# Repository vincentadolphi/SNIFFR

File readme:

SNIFFR® by Studio IKG

The SNIFFR® is a multifunctional sensorplatform designed to monitor and communicate airquality.
In an effort to increase ventilation window and decrease aerosols.

If there's no vague vase in your life, it's not worth it.
~ Studio IKG

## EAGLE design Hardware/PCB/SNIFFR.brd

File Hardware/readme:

All files have been created with Rhino6.

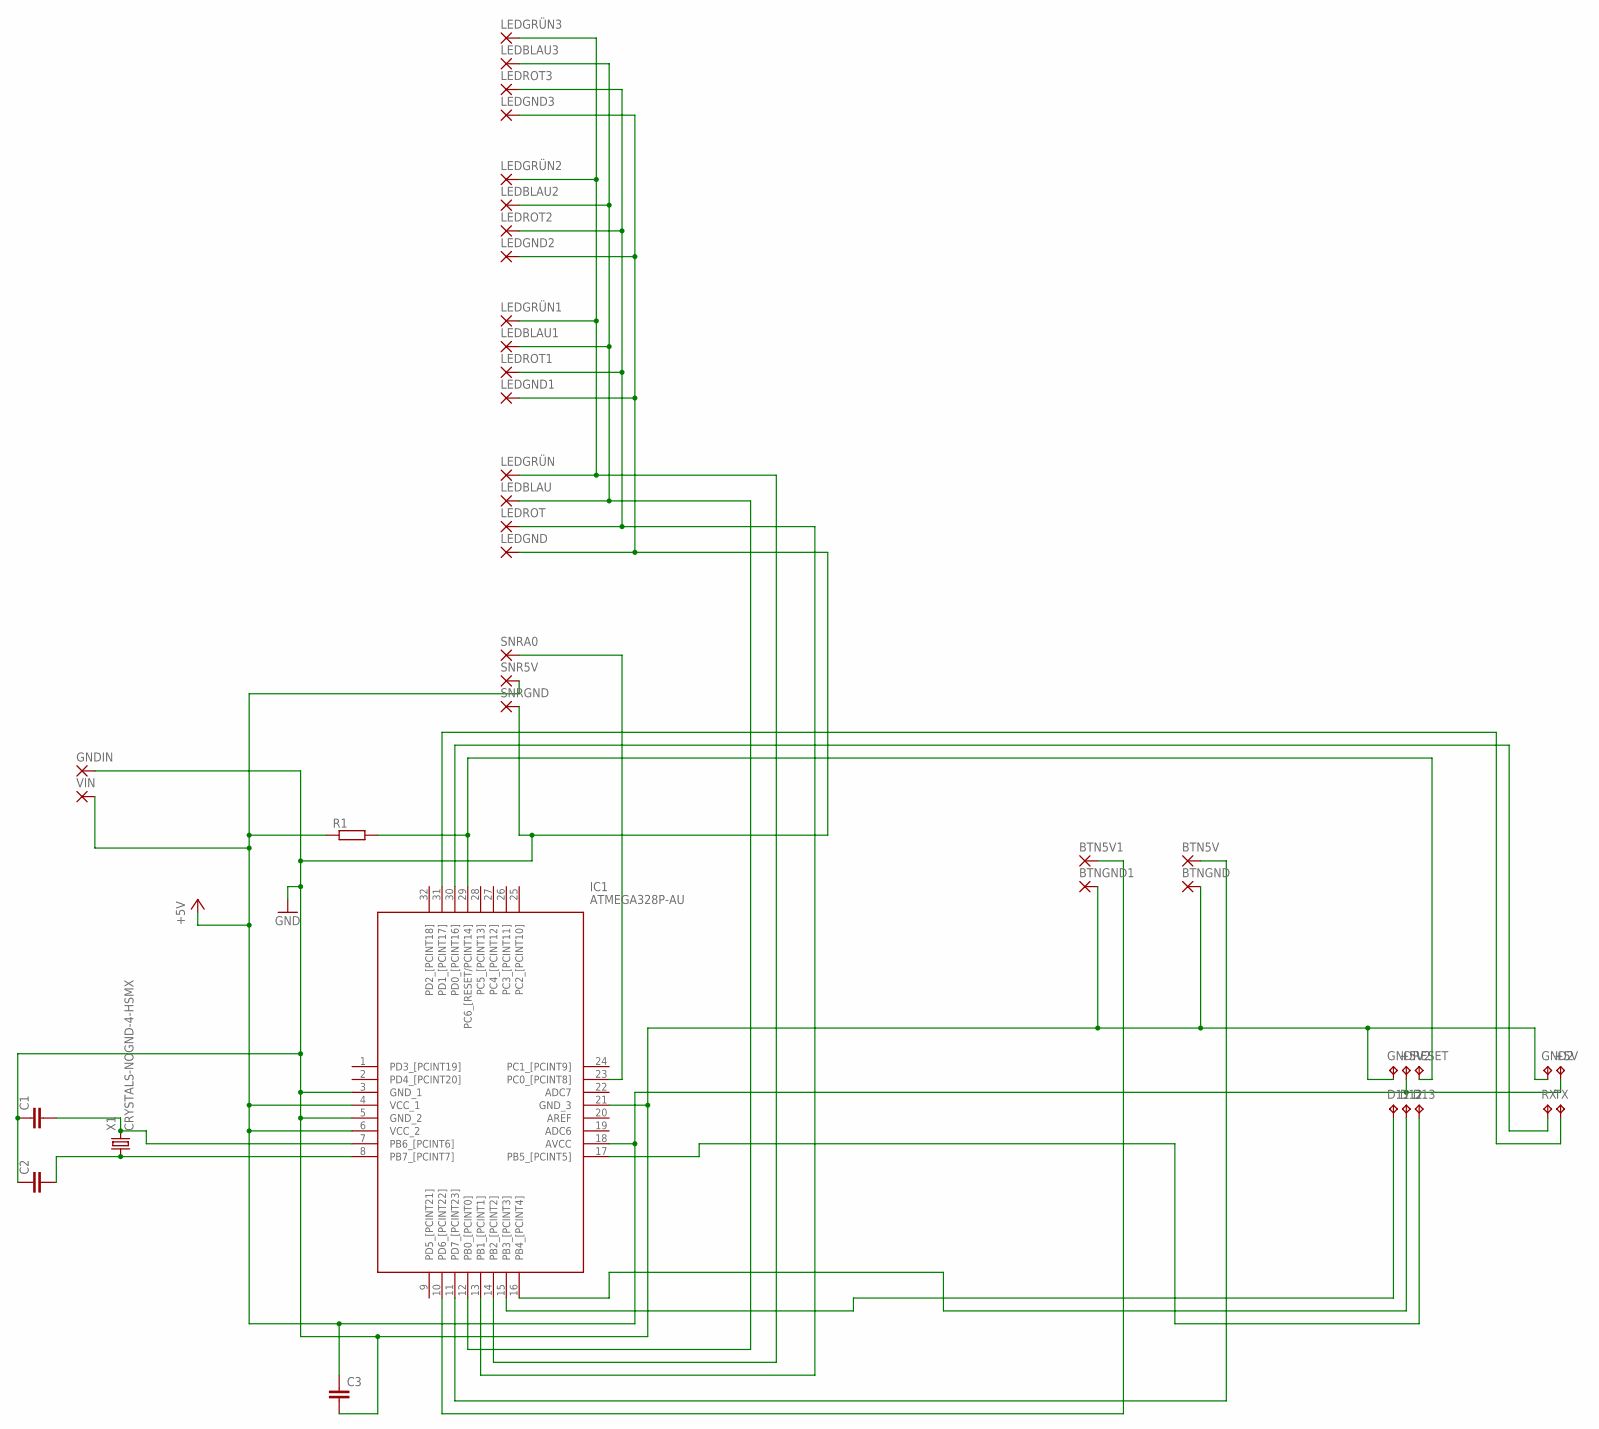
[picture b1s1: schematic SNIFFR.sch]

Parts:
+5V, +5V2: TPTP15SQ; TP15SQ
BTN5V, BTN5V1: 2,15/1,0
BTNGND, BTNGND1: 2,15/1,0
C1, C2, C3: C-EUC0805; C0805
D11, D12, D13: TPTP15SQ; TP15SQ
GND, GND2: TPTP15SQ; TP15SQ
GNDIN: 2,15/1,0
IC1: ATMEGA328P-AU; QFP80P900X900X120-32N
LEDBLAU, LEDBLAU1, LEDBLAU2, LEDBLAU3: 2,15/1,0
LEDGND, LEDGND1, LEDGND2, LEDGND3: 2,15/1,0
LEDGRÜN, LEDGRÜN1, LEDGRÜN2, LEDGRÜN3: 2,15/1,0
LEDROT, LEDROT1, LEDROT2, LEDROT3: 2,15/1,0
R1: R-EU_R0805; R0805
RESET: TPTP15SQ; TP15SQ
RX: TPTP15SQ; TP15SQ
SNR5V: 2,15/1,0
SNRA0: 2,15/1,0
SNRGND: 2,15/1,0
TX: TPTP15SQ; TP15SQ
VIN: 2,15/1,0
X1: CRYSTALS-NOGND-4-HSMX; HC49-4-HSMX

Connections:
+5V: +5V.TP, +5V2.TP, C3.1, IC1.4 (VCC_1), IC1.6 (VCC_2), IC1.18 (AVCC), R1.1, SNR5V.1, VIN.1
GND: BTNGND.1, BTNGND1.1, C1.1, C2.1, C3.2, GND.TP, GND2.TP, GNDIN.1, IC1.3 (GND_1), IC1.5 (GND_2), IC1.21 (GND_3), LEDGND.1, LEDGND1.1, LEDGND2.1, LEDGND3.1, SNRGND.1
unnamed: BTN5V1.1, IC1.10 (PD6_[PCINT22])
unnamed: IC1.29 (PC6_[RESET/PCINT14]), R1.2, RESET.TP
unnamed: C1.2, IC1.7 (PB6_[PCINT6]), X1.2
unnamed: C2.2, IC1.8 (PB7_[PCINT7]), X1.1
unnamed: IC1.13 (PB1_[PCINT1]), LEDROT.1, LEDROT1.1, LEDROT2.1, LEDROT3.1
unnamed: IC1.14 (PB2_[PCINT2]), LEDGRÜN.1, LEDGRÜN1.1, LEDGRÜN2.1, LEDGRÜN3.1
unnamed: IC1.12 (PB0_[PCINT0]), LEDBLAU.1, LEDBLAU1.1, LEDBLAU2.1, LEDBLAU3.1
unnamed: IC1.23 (PC0_[PCINT8]), SNRA0.1
unnamed: D11.TP, IC1.15 (PB3_[PCINT3])
unnamed: D12.TP, IC1.16 (PB4_[PCINT4])
unnamed: D13.TP, IC1.17 (PB5_[PCINT5])
unnamed: IC1.30 (PD0_[PCINT16]), RX.TP
unnamed: IC1.31 (PD1_[PCINT17]), TX.TP
unnamed: BTN5V.1, IC1.11 (PD7_[PCINT23])

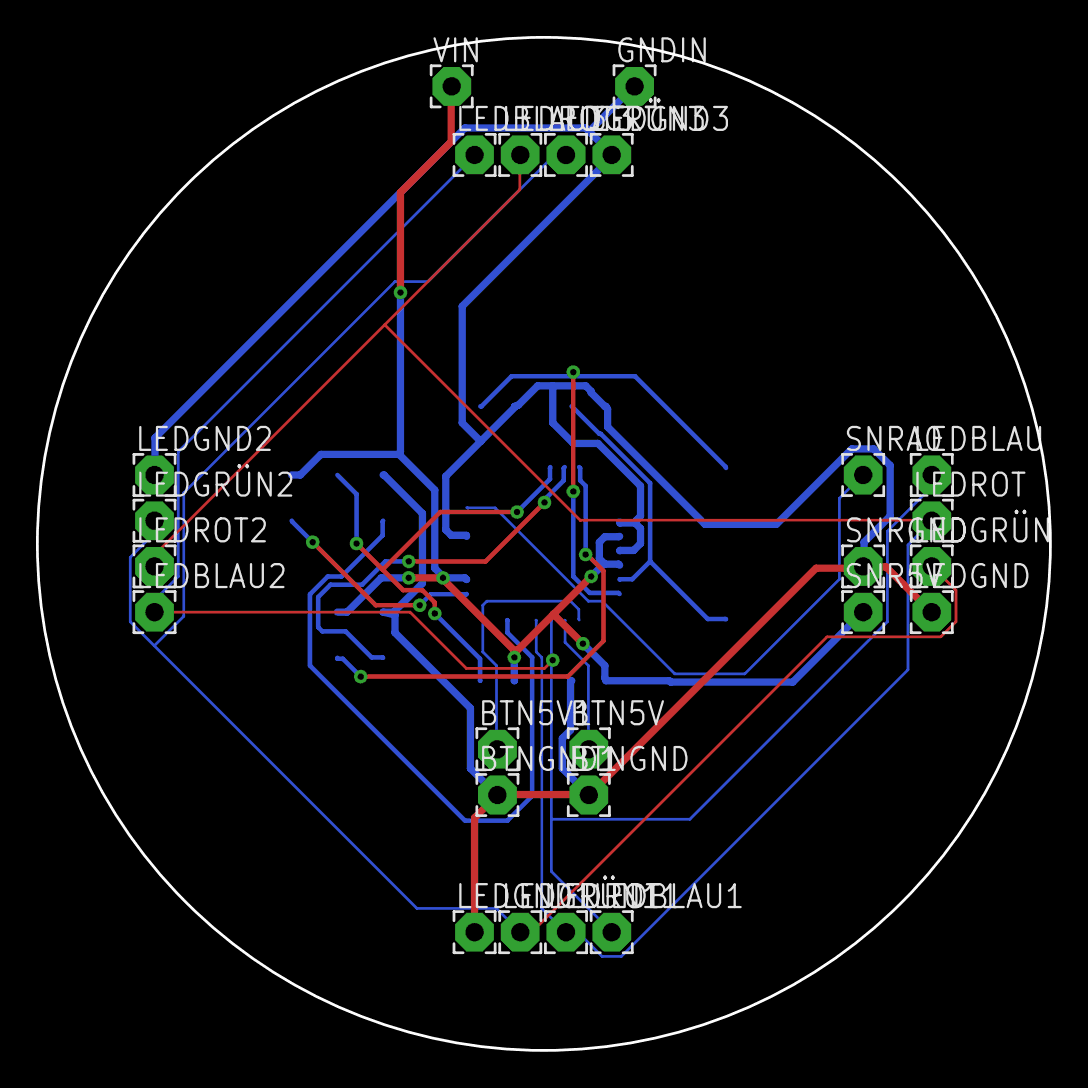
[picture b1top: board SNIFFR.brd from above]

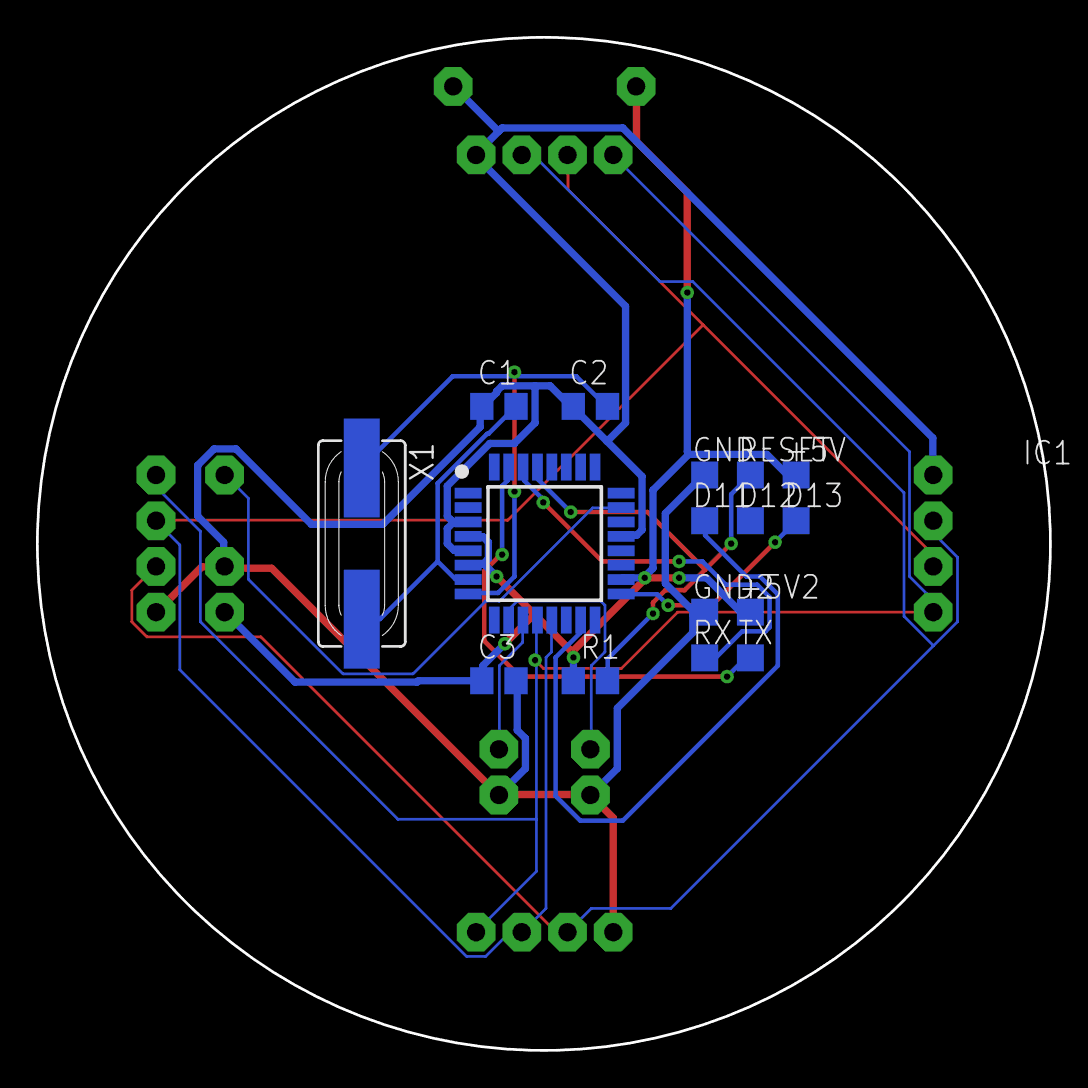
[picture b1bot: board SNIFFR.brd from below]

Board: 2 copper layers, 56.3 x 56.3 mm, 41 parts (16 on the bottom side), 16 nets.

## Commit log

2020-11-14 added readme
2020-11-14 changed readme
2020-11-15 added STLs
2020-11-15 added 3D-Model
2020-11-15 changed screw hole size
2020-11-15 added cut-out for micro-usb-pcb
2020-11-16 added logic diagram
2020-11-16 added SNIFFRos v1
2020-11-16 added EAGLE PCB
2020-11-16 Create LICENSE
    added LICENSE
2020-11-16 Create LICENSE
2020-11-17 added hole for power cord
2021-05-07 redefine variable names for the LEDs
2021-05-07 change the conditions for switching on different LEDs
